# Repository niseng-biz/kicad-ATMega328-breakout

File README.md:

# kicad-ATMega328-breakout

KiCadの使い方演習として作成した図面です。
回路図、PCB図面が含まれています。

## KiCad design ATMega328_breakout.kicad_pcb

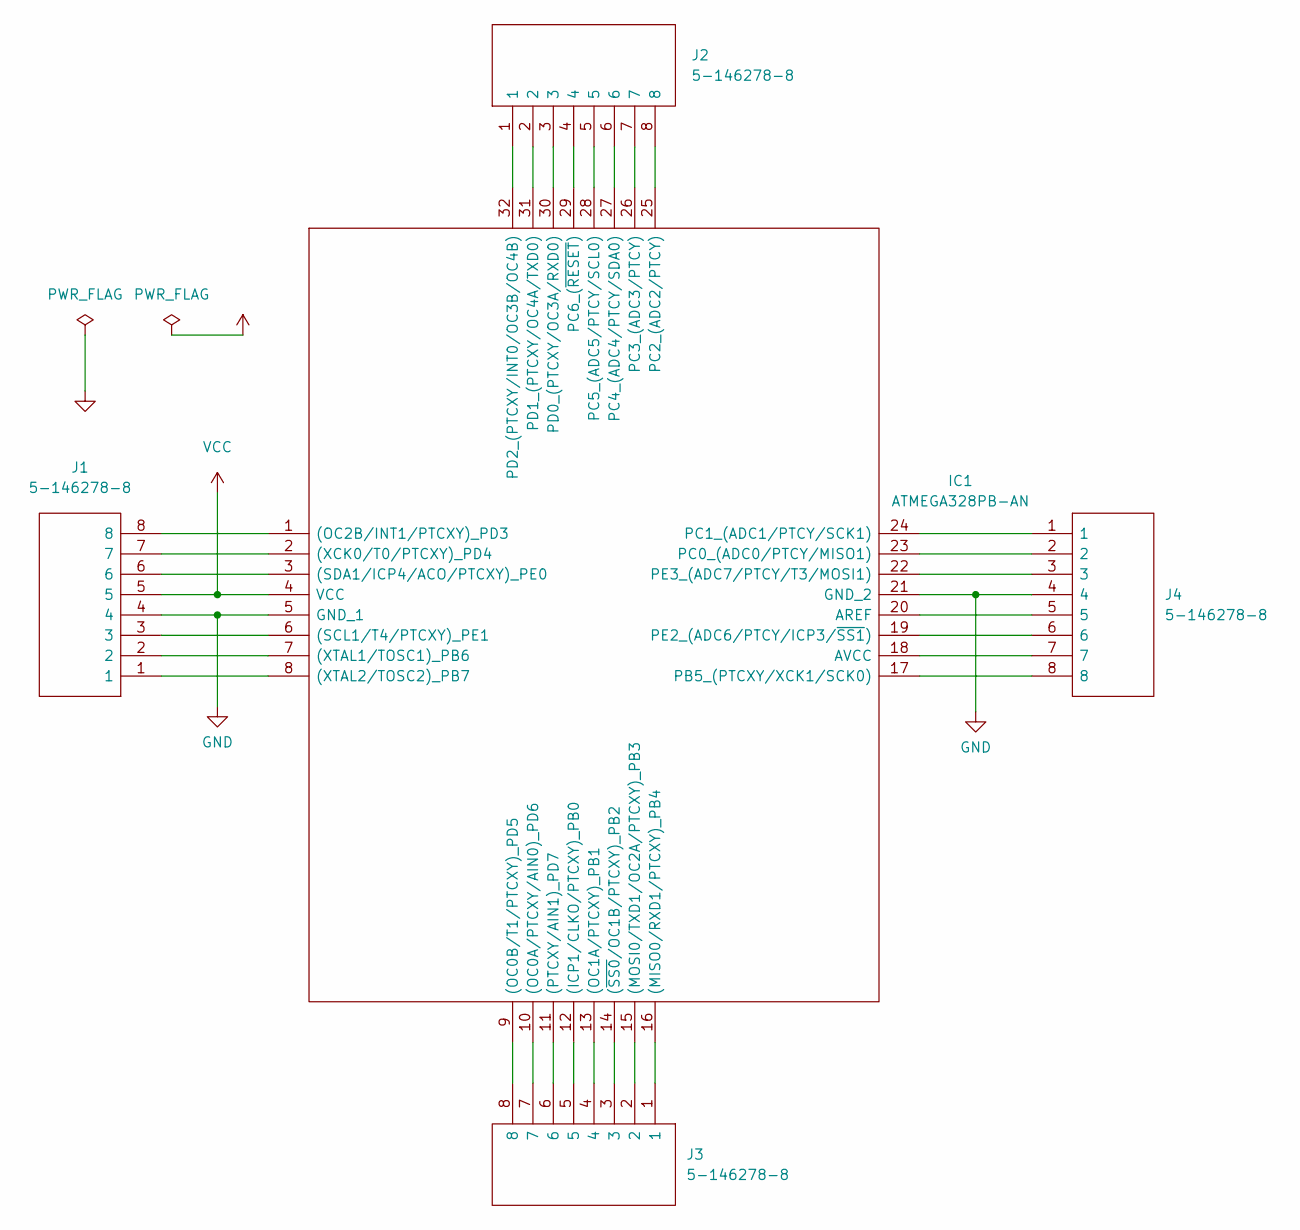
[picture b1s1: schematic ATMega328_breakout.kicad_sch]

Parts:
IC1: ATMEGA328PB-AN; QFP80P900X900X120-32N; Mouser Part Number 556-ATMEGA328PB-AN
J1, J2, J3, J4: 5-146278-8; HDRV8W56P0X254_1X8_1991X234X872P; Mouser Part Number 571-5-146278-8

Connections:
GND: IC1.5 (GND_1), IC1.21 (GND_2), J1.4, J4.4
unnamed: IC1.1 ((OC2B/INT1/PTCXY)_PD3), J1.8
unnamed: IC1.2 ((XCK0/T0/PTCXY)_PD4), J1.7
unnamed: IC1.3 ((SDA1/ICP4/ACO/PTCXY)_PE0), J1.6
unnamed: IC1.6 ((SCL1/T4/PTCXY)_PE1), J1.3
unnamed: IC1.7 ((XTAL1/TOSC1)_PB6), J1.2
unnamed: IC1.8 ((XTAL2/TOSC2)_PB7), J1.1
unnamed: IC1.9 ((OC0B/T1/PTCXY)_PD5), J3.8
unnamed: IC1.10 ((OC0A/PTCXY/AIN0)_PD6), J3.7
unnamed: IC1.11 ((PTCXY/AIN1)_PD7), J3.6
unnamed: IC1.12 ((ICP1/CLKO/PTCXY)_PB0), J3.5
unnamed: IC1.13 ((OC1A/PTCXY)_PB1), J3.4
unnamed: IC1.14 ((~SS0/OC1B/PTCXY)_PB2), J3.3
unnamed: IC1.15 ((MOSI0/TXD1/OC2A/PTCXY)_PB3), J3.2
unnamed: IC1.16 ((MISO0/RXD1/PTCXY)_PB4), J3.1
unnamed: IC1.17 (PB5_(PTCXY/XCK1/SCK0)), J4.8
unnamed: IC1.18 (AVCC), J4.7
unnamed: IC1.19 (PE2_(ADC6/PTCY/ICP3/~SS1)), J4.6
unnamed: IC1.20 (AREF), J4.5
unnamed: IC1.22 (PE3_(ADC7/PTCY/T3/MOSI1)), J4.3
unnamed: IC1.23 (PC0_(ADC0/PTCY/MISO1)), J4.2
unnamed: IC1.24 (PC1_(ADC1/PTCY/SCK1)), J4.1
unnamed: IC1.25 (PC2_(ADC2/PTCY)), J2.8
unnamed: IC1.26 (PC3_(ADC3/PTCY)), J2.7
unnamed: IC1.27 (PC4_(ADC4/PTCY/SDA0)), J2.6
unnamed: IC1.28 (PC5_(ADC5/PTCY/SCL0)), J2.5
unnamed: IC1.29 (PC6_(~RESET)), J2.4
unnamed: IC1.30 (PD0_(PTCXY/OC3A/RXD0)), J2.3
unnamed: IC1.31 (PD1_(PTCXY/OC4A/TXD0)), J2.2
unnamed: IC1.32 (PD2_(PTCXY/INT0/OC3B/OC4B)), J2.1
VCC: IC1.4 (VCC), J1.5

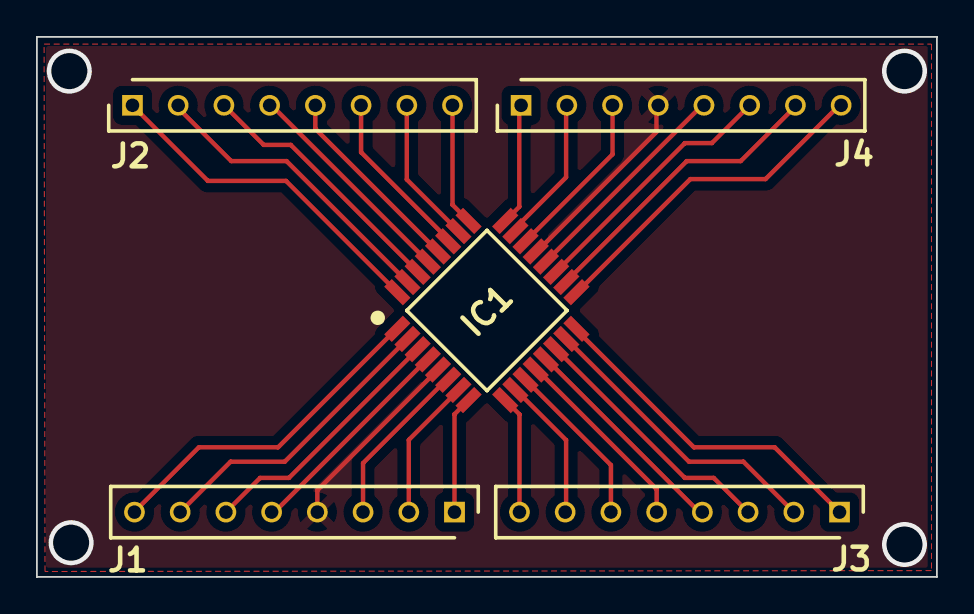
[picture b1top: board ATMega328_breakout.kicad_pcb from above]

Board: 2 copper layers, 50.0 x 30.0 mm, 5 parts (0 on the bottom side), 31 nets.

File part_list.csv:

"Source:","C:\Work\CAD\MCU_Board\HSD_LSD_SENS\ATMega328_breakout\ATMega328_breakout.kicad_sch"
"Date:","2022/08/04 23:26:13"
"Tool:","Eeschema (6.0.4)"
"Generator:","C:\Program Files\KiCad\6.0\bin\scripting\plugins/bom_csv_grouped_by_value.py"
"Component Count:","5"

"Individual Components:"

"Item","Qty","Reference(s)","Value","LibPart","Footprint","Datasheet","Description","Height","Manufacturer_Name","Manufacturer_Part_Number","Mouser Part Number","Mouser Price/Stock"
"","","IC1","ATMEGA328PB-AN","SamacSys_Parts:ATMEGA328PB-AN","QFP80P900X900X120-32N","http://ww1.microchip.com/downloads/en/DeviceDoc/40001906C.pdf","MCU 8-bit ATmega AVR RISC 32KB Flash 2.5V/3.3V/5V 32-Pin TQFP Tray","1.2","Microchip","ATMEGA328PB-AN","556-ATMEGA328PB-AN","https://www.mouser.co.uk/ProductDetail/Microchip-Technology-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"
"","","J1","5-146278-8","SamacSys_Parts:5-146278-8","HDRV8W56P0X254_1X8_1991X234X872P","https://componentsearchengine.com/Datasheets/1/5-146278-8.pdf","08 MODII HDR SRST B/A .100CL","8.72","TE Connectivity","5-146278-8","571-5-146278-8","https://www.mouser.com/Search/Refine.aspx?Keyword=571-5-146278-8"
"","","J2","5-146278-8","SamacSys_Parts:5-146278-8","HDRV8W56P0X254_1X8_1991X234X872P","https://componentsearchengine.com/Datasheets/1/5-146278-8.pdf","08 MODII HDR SRST B/A .100CL","8.72","TE Connectivity","5-146278-8","571-5-146278-8","https://www.mouser.com/Search/Refine.aspx?Keyword=571-5-146278-8"
"","","J3","5-146278-8","SamacSys_Parts:5-146278-8","HDRV8W56P0X254_1X8_1991X234X872P","https://componentsearchengine.com/Datasheets/1/5-146278-8.pdf","08 MODII HDR SRST B/A .100CL","8.72","TE Connectivity","5-146278-8","571-5-146278-8","https://www.mouser.com/Search/Refine.aspx?Keyword=571-5-146278-8"
"","","J4","5-146278-8","SamacSys_Parts:5-146278-8","HDRV8W56P0X254_1X8_1991X234X872P","https://componentsearchengine.com/Datasheets/1/5-146278-8.pdf","08 MODII HDR SRST B/A .100CL","8.72","TE Connectivity","5-146278-8","571-5-146278-8","https://www.mouser.com/Search/Refine.aspx?Keyword=571-5-146278-8"



"Collated Components:"

"Item","Qty","Reference(s)","Value","LibPart","Footprint","Datasheet","Description","Height","Manufacturer_Name","Manufacturer_Part_Number","Mouser Part Number","Mouser Price/Stock"
"1","1","IC1","ATMEGA328PB-AN","SamacSys_Parts:ATMEGA328PB-AN","QFP80P900X900X120-32N","http://ww1.microchip.com/downloads/en/DeviceDoc/40001906C.pdf","MCU 8-bit ATmega AVR RISC 32KB Flash 2.5V/3.3V/5V 32-Pin TQFP Tray","1.2","Microchip","ATMEGA328PB-AN","556-ATMEGA328PB-AN","https://www.mouser.co.uk/ProductDetail/Microchip-Technology-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"
"2","4","J1, J2, J3, J4","5-146278-8","SamacSys_Parts:5-146278-8","HDRV8W56P0X254_1X8_1991X234X872P","https://componentsearchengine.com/Datasheets/1/5-146278-8.pdf","08 MODII HDR SRST B/A .100CL","8.72","TE Connectivity","5-146278-8","571-5-146278-8","https://www.mouser.com/Search/Refine.aspx?Keyword=571-5-146278-8"
